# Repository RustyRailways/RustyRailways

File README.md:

# Rusty Railways

## Description

Group Project by [**lucaSartore** (Sartore Luca)](https://github.com/lucaSartore), [**cattai-lorenzo** (Cattai Lorenzo)](https://github.com/cattai-lorenzo), [**MrLakige** (Callegari Michele)](https://github.com/MrLakige), [**Technorico** (Peruzzo Federico)](https://github.com/Technorico)
for [Embedded Software for The Internet of Things - 145996](https://unitn.coursecatalogue.cineca.it/insegnamenti/2023/95013/2019/10002/10712?annoOrdinamento=2019) taught by professor [Kasim Sinan Yildirim](https://webapps.unitn.it/du/it/Persona/PER0212812/Didattica) at [University of Trento, DISI Department](https://www.disi.unitn.it/).

This is a system that automates the motion of Lego trains and rail switches.
You can tell the system in which station you want a train to go (either using an HTTP request or using our GUI),
and the system will figure out the best way to achieve the goal, even moving trains that are on your
way if necessary. 

## Video

## Components

The system is implemented using 5 different components:

 - `The Master`: This is the component that does all the calculations to find the optimal path, and then controls the trains and the switches, you can learn more about the master [here](./master/readme.md)
 - `The Client`: ([Godot](https://godotengine.org/) based client to create the train track and control/monitor the train system), you can learn more about the client [here](./client/README.md)
 - `The Map`: The map is a support data structure (a modified graph in particular) used by the master, you can learn more about the master [here](./map/readme.md)
 - `The Common Infrastructure`: The common infrastructure defines some basic messages that all components need to communicate with each other, as well as the IPs and the hardware abstraction layer traits, you can learn more about the master [here](./common_infrastructure/readme.md)
 - `The Trains`: You can learn more about the code that manages the trains [here](./train/rust/readme.md)
 - `The Switches`: You can learn more about the code that manages the switches [here](./switch/readme.md)

## Documentation

- [Common infrastructure documentation](https://rustyrailways.github.io/RustyRailways/common_infrastructure/doc/common_infrastructure/index.html)
- [Map documentation](https://rustyrailways.github.io/RustyRailways/map/doc/map/index.html)
- [Master documentation](https://rustyrailways.github.io/RustyRailways/master/doc/master/index.html)
- [Railway sim map documentation](https://rustyrailways.github.io/RustyRailways/railway_sim_map/doc/railway_sim_map/index.html)<br>
- [Switch documentation](https://rustyrailways.github.io/RustyRailways/switch/html/index.html)<br>
- [Train documentation](https://rustyrailways.github.io/RustyRailways/train/doc/locomotive/index.html)<br>

## Installation

Here you can find a quick list of the things you need to do, to try our project yourself.

### Master Installation
The current implementation of the master runs on a Linux system (e.g. Raspberry Pi with Raspberry Pi OS) so to run it, you just need to install the [regular rust toolchain](https://www.rust-lang.org/tools/install).
Given that we used a Hardware Abstraction Layer (HAL) to implement the master, with a bit more work, it can be executed on something smaller (like an ESP-32), if you are interested in this you can check out the train toolchain installation down below. 

### Train Toolchain Installation
The train code is written in embedded rust, with the [embedded-hal](https://github.com/rust-embedded/embedded-hal) and [embedded-svc](https://github.com/esp-rs/embedded-svc/tree/master) crates. To install the software needed to build for our target (The ESP-32) you can follow the tutorial [here](https://github.com/esp-rs/esp-idf-template?tab=readme-ov-file#prerequisites).

### Switch Toolchain Installation
To compile the switch code you can follow [this](./switch/readme.md) tutorial we have written.

### Client Installation
See [Client README.md](https://github.com/MrLakige/rusty_railways/blob/main/client/README.md).

### 3D Printing
Files to print the switch mechanism are located [here](./switch/hardware/Switch_3D_print/)
You can find a 3D printing tutorial [here](https://all3dp.com/1/cura-tutorial-software-slicer-cura-3d/).  

### Electronic Components

To build the switch PCB you can follow [this](switch#pcb) tutorial we have written

### Special Thanks

[FabLab UniTn](https://fablab.unitn.it/) for the space, tools and part of the materials used

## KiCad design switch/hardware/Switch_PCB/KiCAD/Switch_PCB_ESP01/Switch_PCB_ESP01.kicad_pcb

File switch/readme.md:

# ESP-8266 Rail Track Switch Control System

This section of the repository contains the source code for an ESP-8266-based rail track switch control system. The code enables the `ESP-8266` to function as a web server, offering control over a servo-driven rail track switch. It is designed to set the correct path for trains.

## Features
- The `ESP-8266` uses a REST API to interface with the other components of the project.
- Switch control commands can be transmitted via HTTP POST requests.

## Hardware
- The system utilizes a Servo motor (specifically, the `MSG90S`) to control the position of the rail track switch.
- WiFi connectivity is established using the built-in wireless functionality of the `ESP-8266` module.

## Code Overview
- The code includes essential libraries such as `ESP8266WiFi`, `WiFiClient`, `ESP8266WebServer`, `Arduino`, `Servo`, and `ArduinoJson`.
- Switch positions are defined based on user-configurable constants.
- The web server responds to HTTP GET requests with information about the switch and handles HTTP POST requests to control the switch position.

## Requirements
- [PlatformIO](https://platformio.org/platformio-ide) (Follow the [guide to download and configure](https://docs.platformio.org/en/latest/core/installation/index.html))
- PlatformIO compiler toolchain (Download [here](https://registry.platformio.org/platforms/platformio/espressif8266/installation))

## Configuration
1. Modify the WiFi credentials by adjusting the `STASSID` and `STAPSK` constants.
2. Specify the switch characteristics by defining the switch name and position angles for the servo in the code.
   (In our demo it is possible to select one of the predefined configurations of the six switches present on the map, using a compiler directive modifiable in the [platformio.ini](./platformio.ini))

## Usage
1. Connect the `ESP-8266` to the rail track switch control mechanism.
2. Flash the firmware using this command:  
   ```bash
      platformio run --target upload`
   ```
### Troubleshooting
#### If a library is not found
1. Run:  
    ```bash
    pio lib install
    pio update
    ```
#### If PlatformIO is not found
1. Ensure that PlatformIO and the toolchain are installed correctly.
2. Verify that the PlatformIO global variable is set.  
   Command:
   ```bash
      source /your_local_path_to/ENV/bin/activate
   ```
## Supported Hardware Parts:
>[!CAUTION]
>⚠️ **BASIC CNC AND ELECTRONICS KNOWLEDGE IS NEEDED TO REPRODUCE BELOW STEPS** ⚠️
### PCB
Files to create the PCBs are located [here](./hardware/Switch_PCB).
#### To Design and Mill a PCB:
You will require the following software:
- [KiCad](https://www.kicad.org/)
- [FlatCAM](http://flatcam.org/)
- GRBL Controller, like [Candle](https://github.com/Denvi/Candle)

#### To mill the PCB of the Switch:
>[!IMPORTANT]
>GRBL Controller or a GCode for CNC/NC controller for your CNC is required.
1. Download the .nc files from [here](./hardware/Switch_PCB/FlatCAM/OutputFiles)
2. Load in the _CNC Program_ / _NC Code Feeder_ the [file](./hardware/Switch_PCB/FlatCAM/OutputFiles/Switch_PCB_ESP01-F_Cu.gbr_cnc_file.nc) with _F_Cu_ in his name, to make the isolation of the traces of the PCB circuit.
3. Then load in this sequence, the following files: [0.8mm](./hardware/Switch_PCB/FlatCAM/OutputFiles/Switch_PCB_ESP01-PTH_0.8mm.drl_cnc.nc), [1.0mm](./hardware/Switch_PCB/FlatCAM/OutputFiles/Switch_PCB_ESP01-PTH_1.0mm.drl_cnc.nc), [Edge_Cuts](./hardware/Switch_PCB/FlatCAM/OutputFiles/Switch_PCB_ESP01-Edge_Cuts.gbr_cutout_cnc.nc).

___
### Images for reference

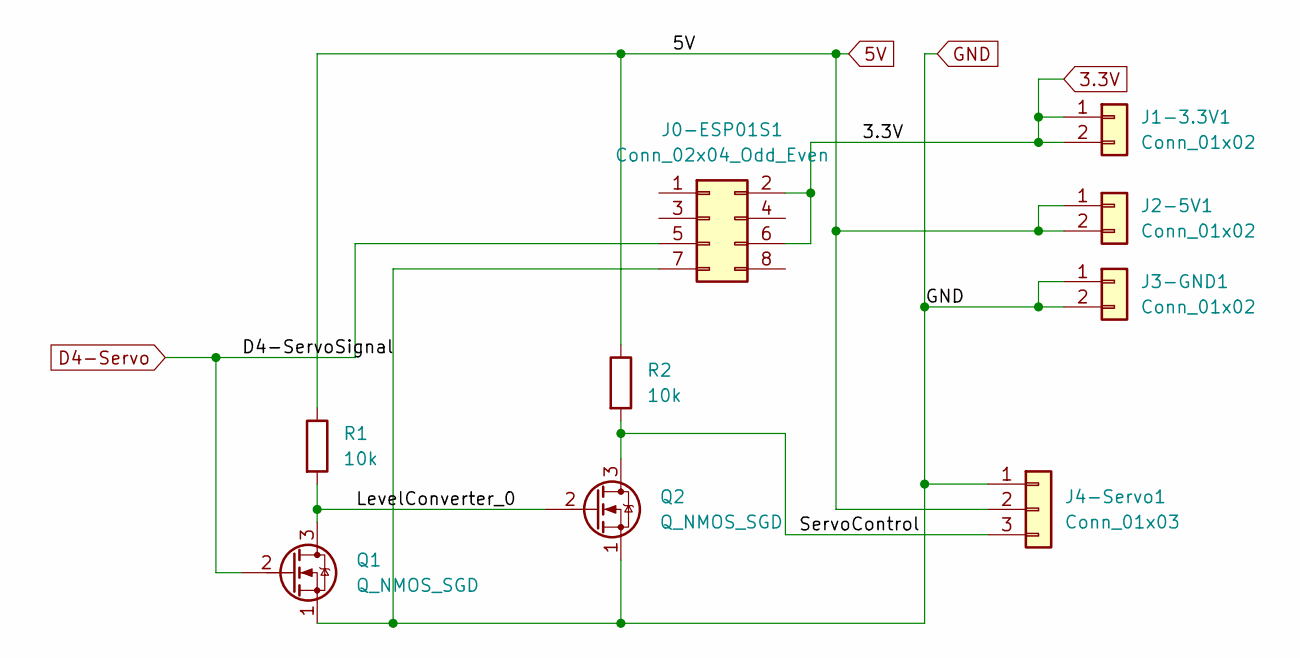
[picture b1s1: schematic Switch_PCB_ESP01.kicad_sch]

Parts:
J0-ESP01S1: Conn_02x04_Odd_Even; ESP01
J1-3.3V1, J2-5V1, J3-GND1: Conn_01x02; 01x02_TerminalBlock
J4-Servo1: Conn_01x03; PinHeader_1x03_P2.54mm_Vertical
Q1, Q2: Q_NMOS_SGD; PinHeader_1x03_P2.54mm_Vertical
R1, R2: 10k; R_Axial_DIN0204_L3.6mm_D1.6mm_P2.54mm_Vertical

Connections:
3.3V: J0-ESP01S1.2, J0-ESP01S1.6, J1-3.3V1.1, J1-3.3V1.2
5V: J2-5V1.1, J2-5V1.2, J4-Servo1.2, R1.1, R2.1
/LevelConverter_0: Q1.3 (D), Q2.2 (G), R1.2
/ServoControl: J4-Servo1.3, Q2.3 (D), R2.2
D4-Servo: J0-ESP01S1.5, Q1.2 (G)
GND: J0-ESP01S1.7, J3-GND1.1, J3-GND1.2, J4-Servo1.1, Q1.1 (S), Q2.1 (S)

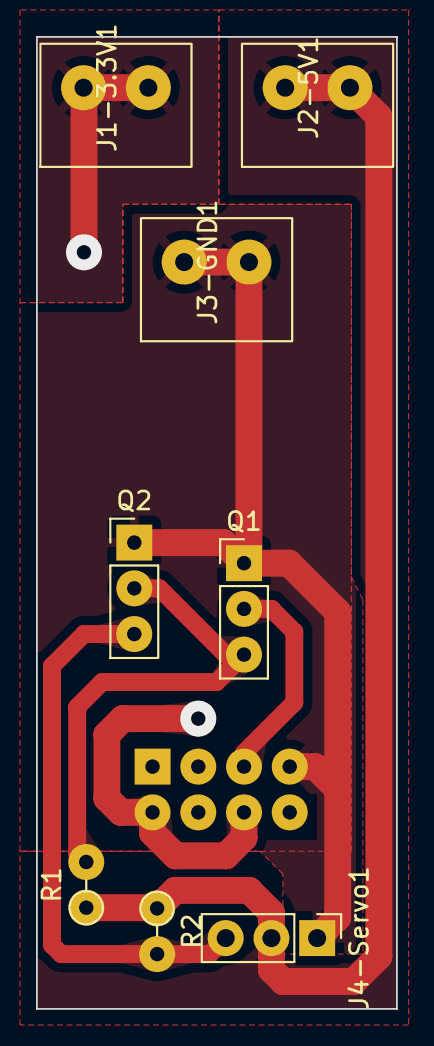
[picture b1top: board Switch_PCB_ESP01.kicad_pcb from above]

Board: 2 copper layers, 20.0 x 54.0 mm, 9 parts (1 on the bottom side), 6 nets.

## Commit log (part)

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2023-10-02 Update README.md
    change name to rusty railways
2023-11-11 add installation requirements
2023-11-11 fix typo
2023-11-11 edit gitignore template
2023-11-11 add examples
2023-11-14 Update requirements.txt
    add new solution for a new problem
2023-11-24 add common infrastructure
2023-11-24 move to generic hart beat
2023-11-25 Add map module
2023-11-25 add simulation stuff
2023-11-25 new file: esp8266/include/README new file: esp8266/lib/README new file: esp8266/platformio.ini new file: esp8266/readme.txt new file: esp8266/src/main.cpp new file: esp8266/test/README
2023-11-27 restructure project
2023-12-10 add simulation map
2023-12-10 add message callback when train moves
2023-12-10 update simulation_map
2023-12-10 fix trait bouds
2023-12-10 add tests
2023-12-10 fix train's is_straight
2023-12-10 add handling of derail error
2023-12-11 add support to wrong cross + test
2023-12-11 remove dead code
2023-12-14 add generic parameter in map struct
2023-12-14 split refeerences into different files
2023-12-14 implement node structure
2023-12-14 add a lifetime to map and propagagte the change
2023-12-14 rename trait for better consistency
2023-12-14 add initialization trait
2023-12-14 add initialization of link
2023-12-14 add initialization of adjacent_nodes
2023-12-14 add init_node_status
2023-12-15 cange from reference to pointer to allow for automatic deserialization
2023-12-15 add node initialization
2023-12-15 add map initialization
2023-12-15 add basic test
2023-12-20 modified: platformio.ini modified: readme.txt new file: src/.main.old.cpp modified: src/main.cpp
    create websocket version
2023-12-20 modified: src/main.cpp
    change port from 81 to 80
2023-12-20 Add swich set option
2023-12-20 add train controller initialization
2023-12-20 modified: src/main.cpp
    now sg90 motor works
2023-12-21 add train direction to train controller
2023-12-21 update creation test
2023-12-21 add error handling to getter methods
2023-12-21 Add map factory
2023-12-21 add hal to map controller view
2023-12-21 move from &str to anyhow::Error for map creation error handling
2023-12-21 finish most map creation view
2023-12-21 fix all warnings
2023-12-22 finish MapCreationView
2023-12-22 add 2 more tests
2023-12-22 add link test
2023-12-22 add switch station tests
2023-12-22 finish map visualization view
2023-12-22 finish map controller view
2023-12-22 fix comments style
2023-12-22 edit map controller apis
2023-12-22 add MapNavigationView
2023-12-24 add heartbeat manager to common infrastructure
2023-12-24 add train direction test
2023-12-24 add low level controller basic functions
2023-12-24 add main file
2023-12-24 add request constructor
2023-12-28 add move recorder
2023-12-29 add navigation functions
2023-12-29 add generic path finder
2023-12-29 add path to position
2023-12-29 add path to intersection function
2023-12-29 add find path to switch point
2023-12-29 add debug print to low level controller
2023-12-29 add scheduler test
2023-12-29 add unsafe move to llc
2023-12-29 fix bug due to priority
2023-12-29 add nota per federico
2024-01-14 Implement master HAL
2024-01-16 add and create train program new file: test/.gitignore new file: test/move/.gitignore new file: test/move/Cargo.toml new file: test/move/build.rs new file: test/move/makefile new file: test/move/part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
2024-01-17 Add template
2024-01-17 add http post test
2024-01-17 add queue
2024-01-18 locomotive rust version modified: test/move/Cargo.toml modified: test/move/src/main.rs deleted: train/Cargo.toml renamed: train/.cargo/config.toml -> train/rust/.cargo/config.toml renamed: train/.git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
2024-01-18 add cpp part, useful for testing new file: train/cpp/.gitignore new file: train/cpp/arduinoWebSockets new file: train/cpp/include/README new file: train/cpp/lib/README new file: train/cpp/platformio.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
2024-01-18 add switch and train control test
    new file: quick_tests/control_test/test.py
    modified: .gitignore
    modified: train/cpp/arduinoWebSockets (modified content)
2024-01-20 add wifi controller
2024-01-20 update toml versions
2024-01-20 add message reciver
2024-01-20 add nfc driver
2024-01-20 add public master ip
2024-01-20 add message sender
2024-01-20 rename file
2024-01-20 fix position type
2024-01-20 edit train hal
2024-01-20 fix warnings
2024-01-20 Final fixes
2024-01-21 minor fixes
2024-01-21 fix IPs
2024-01-22 Add SetSpeedAndStopAt message management
2024-01-22 Switch part
    new file: switch/include/README
    new file: switch/lib/README
    new file: switch/platformio.ini
    new file: switch/readme.txt
    new file: switch/src/.main.old.cpp
    new file: switch/src/main.cpp
2024-01-23 Add wifi credentials
2024-01-23 add wifi credentals
2024-01-23 add high level controller form stdin
2024-01-23 update master url
2024-01-24 add train url
2024-01-24 temp fix
2024-01-24 fix minor bugs
2024-01-25 update positions
2024-01-25 use standard library
2024-01-27 update gitignore
2024-01-27 move map to separate module
2024-01-27 add from and to primitive traits
2024-01-28 add to json function
2024-01-28 Add dynamic lib for map creation
2024-01-28 Add comunicator for multithreadedd map creation
2024-01-28 add missing file to map crate
2024-01-28 Add comunicator constructor
2024-01-28 fix missed import
2024-01-28 Add and test lock-unlock feature
2024-01-31 Add pio to gitignore
2024-01-31 add .pio to gitignore
2024-01-31 minor changes
2024-01-31 Add angle s2
2024-01-31 modified: switch/angles.txt
2024-01-31 bug fixing 1 modified: src/main.cpp
2024-01-31 bug fixed, host name modified: platformio.ini modified: src/main.cpp
2024-01-31 Remove OTA because it cause some critial errors modified: switch/platformio.ini modified: switch/src/main.cpp
2024-01-31 modified: switch/platformio.ini
2024-01-31 set speed off set for locomotive n2
2024-01-31 Add better switching low level controller
2024-01-31 last changes
2024-01-31 Add switch 3
2024-01-31 Fix typo in README.md
2024-01-31 Add client directory and basic README.md for the client part
2024-01-31 Add client/train-track-pieces directory and some placeholder low quality images for now
2024-01-31 Add image to remember what parameters to use when generating CollisionPolygon2Ds for the train track pieces
2024-01-31 Add BaseTrainTrackPiece (base reference Node for all train track pieces)
2024-01-31 Add Godot .import files for all client/train-track-piece images
2024-01-31 Add SwitchHalfCurve and SwitchHalfCurveFlippedVertically nodes in client/train-track-pieces
2024-01-31 Add QuarterStraight node in client/train-track-pieces
2024-01-31 Add HalfStraight node in client/train-track-pieces
2024-01-31 Add LongCurve and LongCurveFlippedVertically nodes in client/train-track-pieces
2024-01-31 Add HalfCurve and HalfCurveFlippedVertically nodes in client/train-track-pieces
2024-01-31 Add Curve and CurveFlippedVertically nodes in client/train-track-pieces
2024-01-31 Add client/nfs-tags directory and a placeholder nfc-tag-card.png image with it's Godot .import file
2024-01-31 Add NFCTag node in client/nfs-tags
2024-01-31 Add client/trains directory and some placeholder train images with their respective Godot .import files
2024-01-31 Add client/screenshots directory and some screenshots of the client in it
2024-01-31 Add screenshots to client/README.md
2024-01-31 Add "Components of the project" section in README.md
2024-01-31 Add logo to README.md
2024-01-31 Update client/README.md description
2024-01-31 Update README.md "Components of the Project" "client" section description
2024-01-31 Add Rusty Railways client logo and relative Godot .import file
2024-01-31 Add client/trash-can directory and a placeholder trash can image with it's Godot .import file
2024-01-31 Add a placeholder trash mode cursor icon image with it's Godot .import file in client
2024-01-31 Add client/screenshots Godot .import files
2024-01-31 Update client/.gitignore with blacklist for ".tmp" files
2024-01-31 Add TrashCan node and relative script in client/trash-can
2024-01-31 Add coi_serviceworker Godot plugin to bypass js SharedArrayBuffer header requirements (https://developer.mozilla.org/en-US/docs/Web/JavaScript/Reference/Global_Objects/SharedArrayBuffer) when buildin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
2024-01-31 Add Train node in client/trains
2024-01-31 Add client/export_presets.cfg (Godot project export/build presets)
2024-01-31 Add client/Main.tscn node
2024-01-31 Add client/WebSocketClient.tscn node (deprecated as we now use HTTP)
2024-01-31 Add client/MainCamera.gd script (allows zooming and panning)
2024-01-31 Add client/AutoDataUpdater.gd script (for automatic updates of the train system status)
2024-01-31 Add debug nodes and scripts to client
2024-01-31 Fix broken dependency in client/Main.tscn
2024-01-31 Add client/build/web directory and latest client web export/build to it
2024-02-01 Change train track spawner locations in client/Main.tscn (they are organized now)
2024-02-01 Removed old autoloaded plugin in client/project.godot
2024-02-01 Add Godot client build script (linux only for now)
2024-02-01 Update client/MainCamera.gd to allow for better control and a different default zoom level
2024-02-01 Add force update connections functionality to client
    now you can build train track in the Godot editor itself, and they will correctly connect together when you run the client!
2024-02-01 Change some Camera settings in client/Main.tscn
2024-02-01 Change tree structure of client/Main.tscn (it's way better now)
2024-02-01 Add SimpleHTTPSServer.py to allow easy testing of the web build of the client
2024-02-01 Update client/build/web to the latest version
2024-02-01 modified: .gitignore deleted: .idea/.gitignore deleted: esp8266/include/README deleted: esp8266/lib/README deleted: esp8266/platformio.ini deleted: esp8266/readme.txt deleted: esp8266/src/.main.old.c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
2024-02-01 Add map readme
2024-02-01 Add common infrastructure readme
2024-02-01 Switch and Train documentation
2024-02-01 Add s2 and s2 IPs
2024-02-01 Finish master readme
2024-02-01 Remove unused dependency
2024-02-01 Add map simulation doc
2024-02-01 Add map doc
2024-02-01 Add train docs
2024-02-02 Internal Godot uid changes of client/Main.tscn
2024-02-02 Add Settings with basic background color changer to client
2024-02-02 Add common infrastructure doc
2024-02-02 Add connection test
2024-02-02 Add map sim readme
2024-02-02 Add documentation index
2024-02-02 change tag
2024-02-06 Fix gui integration
2024-02-06 Gui FIX
2024-02-06 Remove sub module
2024-02-06 remove unecessary doctype
2024-02-06 rename folder
2024-02-06 update main readme
2024-02-06 Update video preview
2024-02-06 fix formatting
2024-02-06 Update installation
2024-02-06 Update README.md
    Add client installation instructions to README.md
2024-02-06 Update client/README.md with basic installation instructions
2024-02-07 fix train readme
2024-02-07 Add of PCB and Board images
2024-02-07 Add KiCAD PCB image
2024-02-07 Add switch board schematic
2024-02-07 Rescale of images
2024-02-07 Add train hardware image
2024-02-07 Rename ConnectionPointSnapArea to SnapArea
2024-02-07 Add SnapArea to NFCTag.tscn node in client
2024-02-07 Add client/video/example-usage.mp4
2024-02-07 Move logo.png to imgs folder
2024-02-07 Fix missclick paste
2024-02-07 Add release code for master
2024-02-07 Fix readme 1/2
2024-02-07 Fix switch readme.md
2024-02-07 Update video
2024-02-07 Remove test folder because it's not useful anymore
2024-02-07 Add master releases
2024-02-07 Fix readme
2024-02-07 Update, grammar correction index.html
2024-02-07 Update, fix documentation README.md
2024-02-07 Add client/video/example-usage-2.mp4
2024-02-07 Update client/README.md videos
2024-02-07 Add fixed pdf file
2024-03-06 Update README.md with better description and special thanks
2024-04-12 Update README.md to reflect username change of Lorenzo Cattai
2024-04-12 Update README.md with new naming format for contributor names
2024-06-18 Update client/README.md with currently broken warning
2024-06-26 Fix broken link in README.md
